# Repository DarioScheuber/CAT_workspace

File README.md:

# CAT_workspace
 HSLU CAT Blockwoche

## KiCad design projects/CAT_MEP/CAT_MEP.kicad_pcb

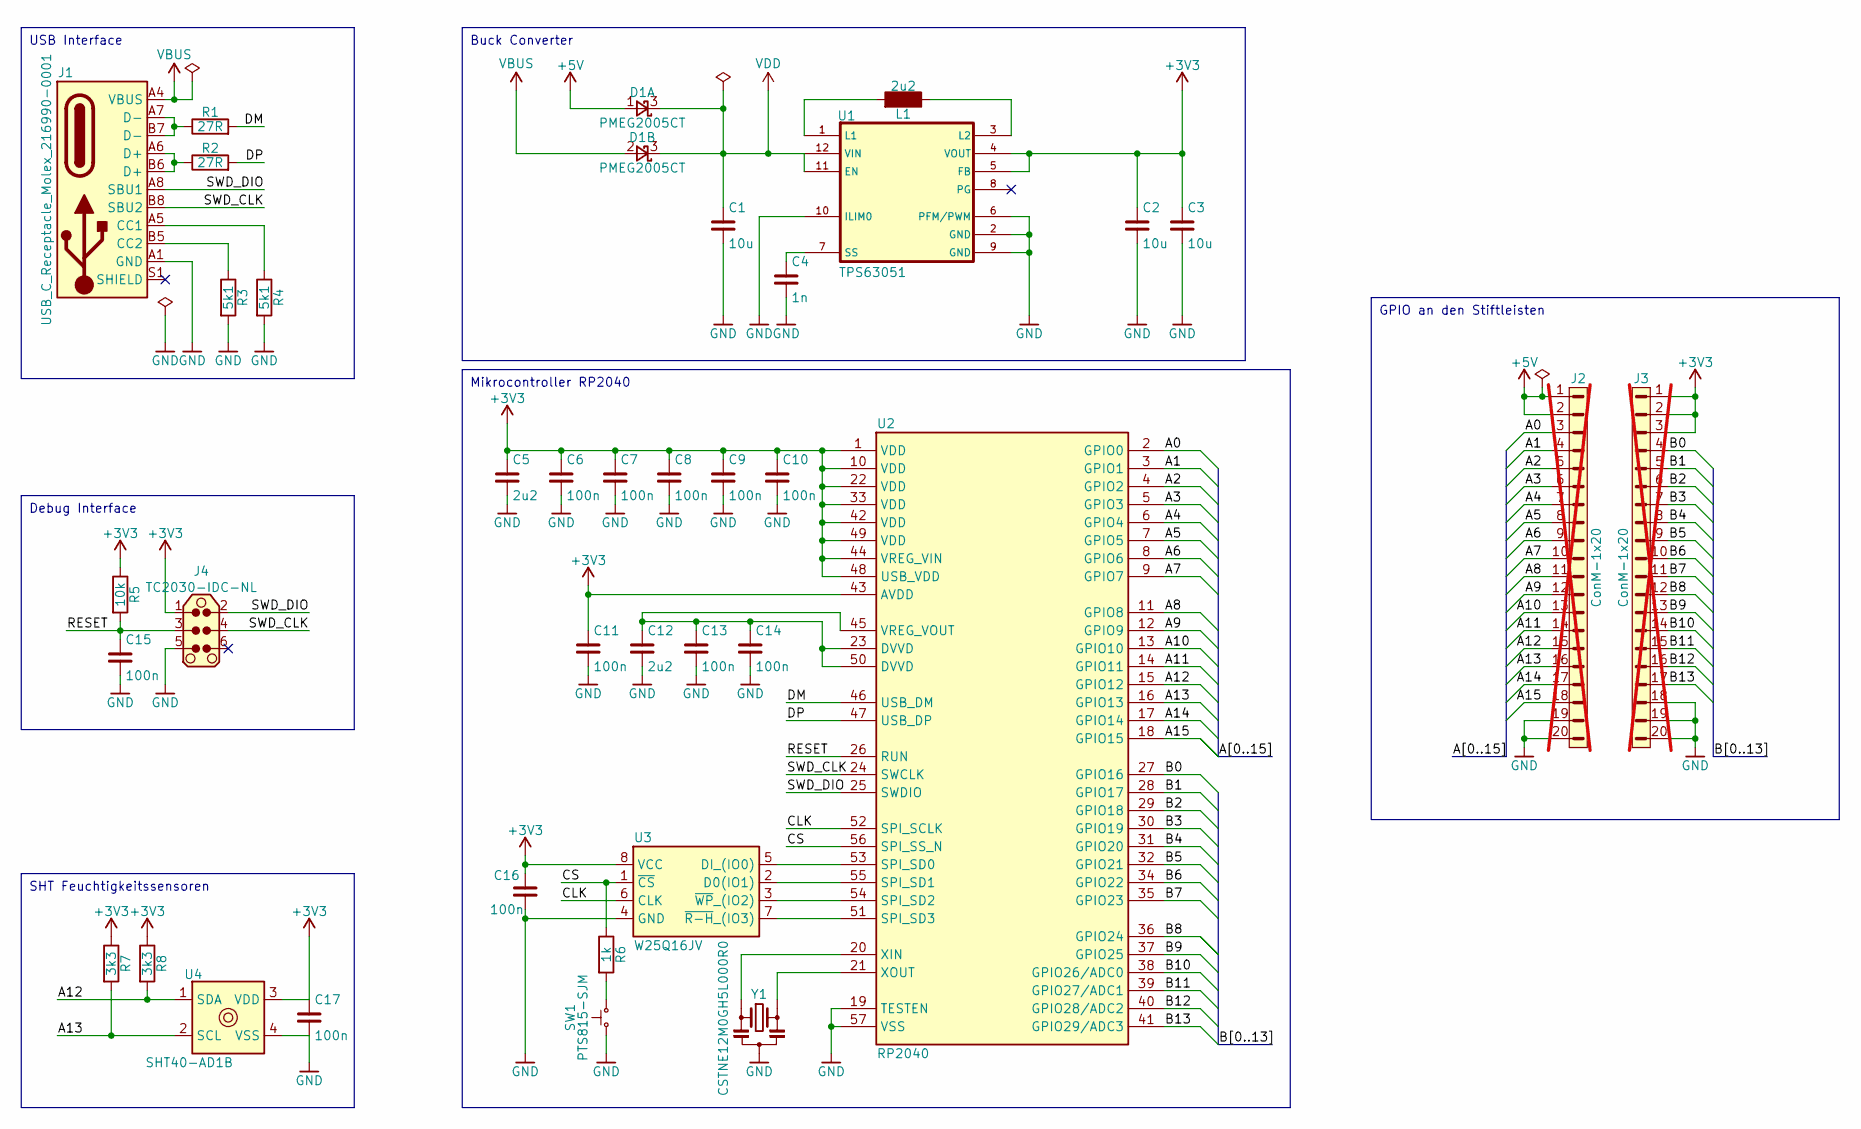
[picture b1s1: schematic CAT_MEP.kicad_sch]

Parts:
C1, C2, C3: 10u; C_0805; Rating 10V, 10%; MFR# CL21B106KPY6PNE
C4: 1n; C_0402; Rating 16V, 10%, X7R; MFR# CL05B102KO5NNWC
C5, C12: 2u2; C_0402; Rating 16V, 10%, X5R; MFR# CL05A225KO5NQNC
C6, C7, C8, C9, C10, C11, C13, C14, C15, C16, C17: 100n; C_0402; Rating 16V, 10%, X7R; MFR# MCASE105SB7104KFNA01
D1: PMEG2005CT; SOT-23; Rating 20V 500mA, Vf360mV, dual (CC) schottky 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; MFR# PMEG2005CT
J1: USB_C_Receptacle_Molex_216990-0001; USB_C_Receptacle_MidMnt_Molex_16_Contact_216990-0001; Rating 16 contacts, 1.25A; MFR# 216990-0001
J2, J3: ConM-1x20; PinHeader_1x20_P2.54mm_Vertical; Rating 1 Row, 2.54mm; MFR# 10129378-920001BLF; not fitted
J4: TC2030-IDC-NL; MFR# TC2030-IDC-NL
L1: 2u2; L_3.2mmx2.5mm; Rating 4A, 20%, 61mOhm; MFR# SRP3212-2R2M
R1, R2: 27R; R_0402; Rating 50V, 62.5mW, 1%; MFR# RC0402FR-0727RL
R3, R4: 5k1; R_0402; Rating 50V, 62.5mW, 1%; MFR# RC0402FR-075K1L
R5: 10k; R_0402; Rating 50V, 62.5mW, 1%; MFR# RC0402FR-0710KL
R6: 1k; R_0402; Rating 50V, 62.5mW, 1%; MFR# RC0402FR-071KL
R7, R8: 3k3; R_0402; Rating 50V, 62.5mW, 1%; MFR# RC0402FR-073K3L
SW1: PTS815-SJM; PTS815-Series; Rating 12VDC, 50mA, 180gf; MFR# PTS815 SJM 250 SMTR LFS
U1: TPS63051; VQFN-12-1EP_2.5x2.5mm_P0.5mm; MFR# TPS63051RMWR
U2: RP2040; QFN-56-1EP_7x7mm_P0.4mm_EP3.2x3.2mm
U3: W25Q16JV; USON_2x3x0.6mm; Rating 3V 16Mbit; MFR# W25Q16JVUXIQ TR
U4: SHT40-AD1B; SHT4x; Rating +/-1.8%RH, +/-0.2°C; MFR# SHT40-AD1B-R3
Y1: CSTNE12M0GH5L000R0; Resonator_SMD_Murata_CSTxExxV-3Pin_3.0x1.1mm; Rating 12MHz, 0.07%; MFR# CSTNE12M0GH5L000R0; mouser# 81-CSTNE12M0GH5L000R

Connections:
+3V3: C2.1, C3.1, C5.1, C6.1, C7.1, C8.1, C9.1, C10.1, C11.1, C16.1, C17.1, J3.1, J3.2, J3.3, J4.1, R5.1, R7.1, R8.1, U1.4 (VOUT), U1.5 (FB), U2.1 (VDD), U2.10 (VDD), U2.22 (VDD), U2.33 (VDD), U2.42 (VDD), U2.43 (AVDD), U2.44 (VREG_VIN), U2.48 (USB_VDD), U2.49 (VDD), U3.8 (VCC), U4.3 (VDD)
+5V: D1.1 (K), J2.1, J2.2
/A0: J2.3, U2.2 (GPIO0)
/A1: J2.4, U2.3 (GPIO1)
/A2: J2.5, U2.4 (GPIO2)
/A3: J2.6, U2.5 (GPIO3)
/A4: J2.7, U2.6 (GPIO4)
/A5: J2.8, U2.7 (GPIO5)
/A6: J2.9, U2.8 (GPIO6)
/A7: J2.10, U2.9 (GPIO7)
/A8: J2.11, U2.11 (GPIO8)
/A9: J2.12, U2.12 (GPIO9)
/A10: J2.13, U2.13 (GPIO10)
/A11: J2.14, U2.14 (GPIO11)
/A12: J2.15, R8.2, U2.15 (GPIO12), U4.1 (SDA)
/A13: J2.16, R7.2, U2.16 (GPIO13), U4.2 (SCL)
/A14: J2.17, U2.17 (GPIO14)
/A15: J2.18, U2.18 (GPIO15)
/B0: J3.4, U2.27 (GPIO16)
/B1: J3.5, U2.28 (GPIO17)
/B2: J3.6, U2.29 (GPIO18)
/B3: J3.7, U2.30 (GPIO19)
/B4: J3.8, U2.31 (GPIO20)
/B5: J3.9, U2.32 (GPIO21)
/B6: J3.10, U2.34 (GPIO22)
/B7: J3.11, U2.35 (GPIO23)
/B8: J3.12, U2.36 (GPIO24)
/B9: J3.13, U2.37 (GPIO25)
/B10: J3.14, U2.38 (GPIO26/ADC0)
/B11: J3.15, U2.39 (GPIO27/ADC1)
/B12: J3.16, U2.40 (GPIO28/ADC2)
/B13: J3.17, U2.41 (GPIO29/ADC3)
/CLK: U2.52 (SPI_SCLK), U3.6 (CLK)
/CS: R6.1, U2.56 (SPI_SS_N), U3.1 (~CS)
/DM: R1.2, U2.46 (USB_DM)
/DP: R2.2, U2.47 (USB_DP)
/RESET: C15.1, J4.3, R5.2, U2.26 (RUN)
/SWD_CLK: J1.B8 (SBU2), J4.4, U2.24 (SWCLK)
/SWD_DIO: J1.A8 (SBU1), J4.2, U2.25 (SWDIO)
GND: C1.2, C2.2, C3.2, C4.2, C5.2, C6.2, C7.2, C8.2, C9.2, C10.2, C11.2, C12.2, C13.2, C14.2, C15.2, C16.2, C17.2, J1.A1 (GND), J2.19, J2.20, J3.18, J3.19, J3.20, J4.5, R3.2, R4.2, SW1.1, U1.2 (GND), U1.6 (PFM/PWM), U1.9 (GND), U1.10 (ILIM0), U2.19 (TESTEN), U2.57 (VSS), U3.4 (GND), U4.4 (VSS), Y1.2
unnamed: J1.A5 (CC1), R4.1
unnamed: J1.B5 (CC2), R3.1
unnamed: J1.A6 (D+), J1.B6 (D+), R2.1
unnamed: J1.A7 (D-), J1.B7 (D-), R1.1
unnamed: R6.2, SW1.2
unnamed: L1.1, U1.1 (L1)
unnamed: L1.2, U1.3 (L2)
unnamed: C4.1, U1.7 (SS)
unnamed: U2.53 (SPI_SD0), U3.5 (DI_(IO0))
unnamed: U2.55 (SPI_SD1), U3.2 (D0(IO1))
unnamed: U2.54 (SPI_SD2), U3.3 (~WP_(IO2))
unnamed: U2.51 (SPI_SD3), U3.7 (~R-H_(IO3))
unnamed: C12.1, C13.1, C14.1, U2.23 (DVVD), U2.45 (VREG_VOUT), U2.50 (DVVD)
unnamed: U2.20 (XIN), Y1.1
unnamed: U2.21 (XOUT), Y1.3
VBUS: D1.2 (K), J1.A4 (VBUS)
VDD: C1.1, D1.3 (K), U1.11 (EN), U1.12 (VIN)

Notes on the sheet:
Debug Interface
USB Interface
Buck Converter
SHT Feuchtigkeitssensoren
Mikrocontroller RP2040
GPIO an den Stiftleisten

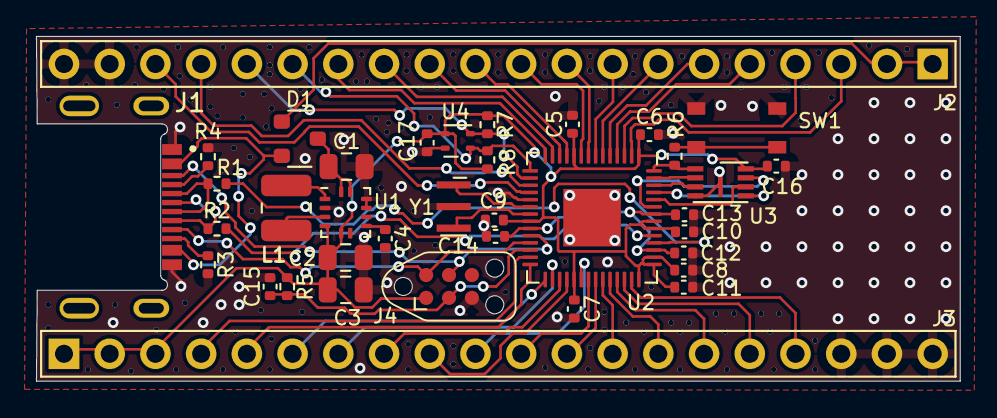
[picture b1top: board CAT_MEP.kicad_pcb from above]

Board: 2 copper layers, 51.3 x 19.2 mm, 37 parts (0 on the bottom side), 57 nets.

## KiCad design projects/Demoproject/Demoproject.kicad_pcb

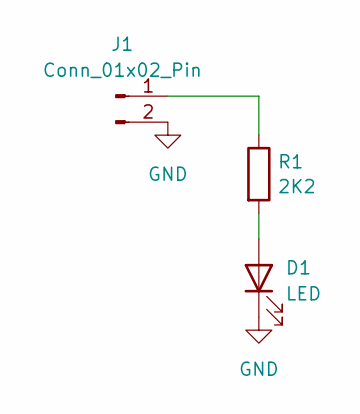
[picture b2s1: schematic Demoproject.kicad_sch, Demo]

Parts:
D1: LED; LED_0805_2012Metric
J1: Conn_01x02_Pin; AMASS_XT30PW-M_1x02_P2.50mm_Horizontal
R1: 2K2; R_0805_2012Metric_Pad1.20x1.40mm_HandSolder

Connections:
GND: D1.1 (K), J1.2
unnamed: D1.2 (A), R1.2
unnamed: J1.1, R1.1

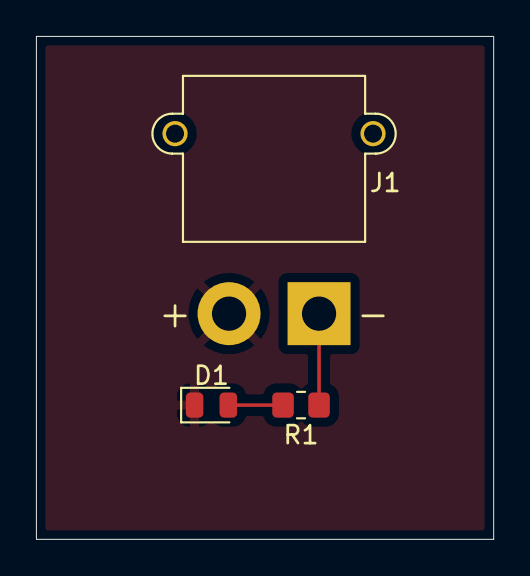
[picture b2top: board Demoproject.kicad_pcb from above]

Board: 2 copper layers, 25.4 x 27.9 mm, 3 parts (0 on the bottom side), 3 nets.

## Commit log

2024-02-12 Ordnerstruktur erstellt
2024-02-12 add Demoproject
2024-02-12 sheet Template
2024-02-13 add new libs
2024-02-14 add database
2024-02-14 add footprint and new database comp
2024-02-14 add new symbols
2024-02-16 add Cat MEP und alle outputjobs
2024-02-16 change project
2024-03-07 add zip lib
